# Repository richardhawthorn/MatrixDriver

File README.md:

### Description

ESP8266 board for driving neopixels arrays - <a href="http://www.matrixpainter.com">matrixpainter.com</a>

### Features

- ESP8266 12/12E Processor
- Power jack for 5v input
- Wifi connected
- Neopixel output (3.3v or 5v)
- Mini USB power connector
- FTDI programming port
- Surface mount

### Instructions

Setup an account at <a href="http://www.matrixpainter.com">matrixpainter.com</a> to start painting your pixels!

### License

This work is licensed under a Creative Commons Attribution-ShareAlike 4.0 International License.

<br />
Designed by <a xmlns:cc="http://creativecommons.org/ns#" href="http://www.richardhawthorn.com" property="cc:attributionName" rel="cc:attributionURL" target="_blank">Richard Hawthorn</a><br />
<a rel="license" href="http://creativecommons.org/licenses/by-sa/4.0/" target="_blank">View License</a>

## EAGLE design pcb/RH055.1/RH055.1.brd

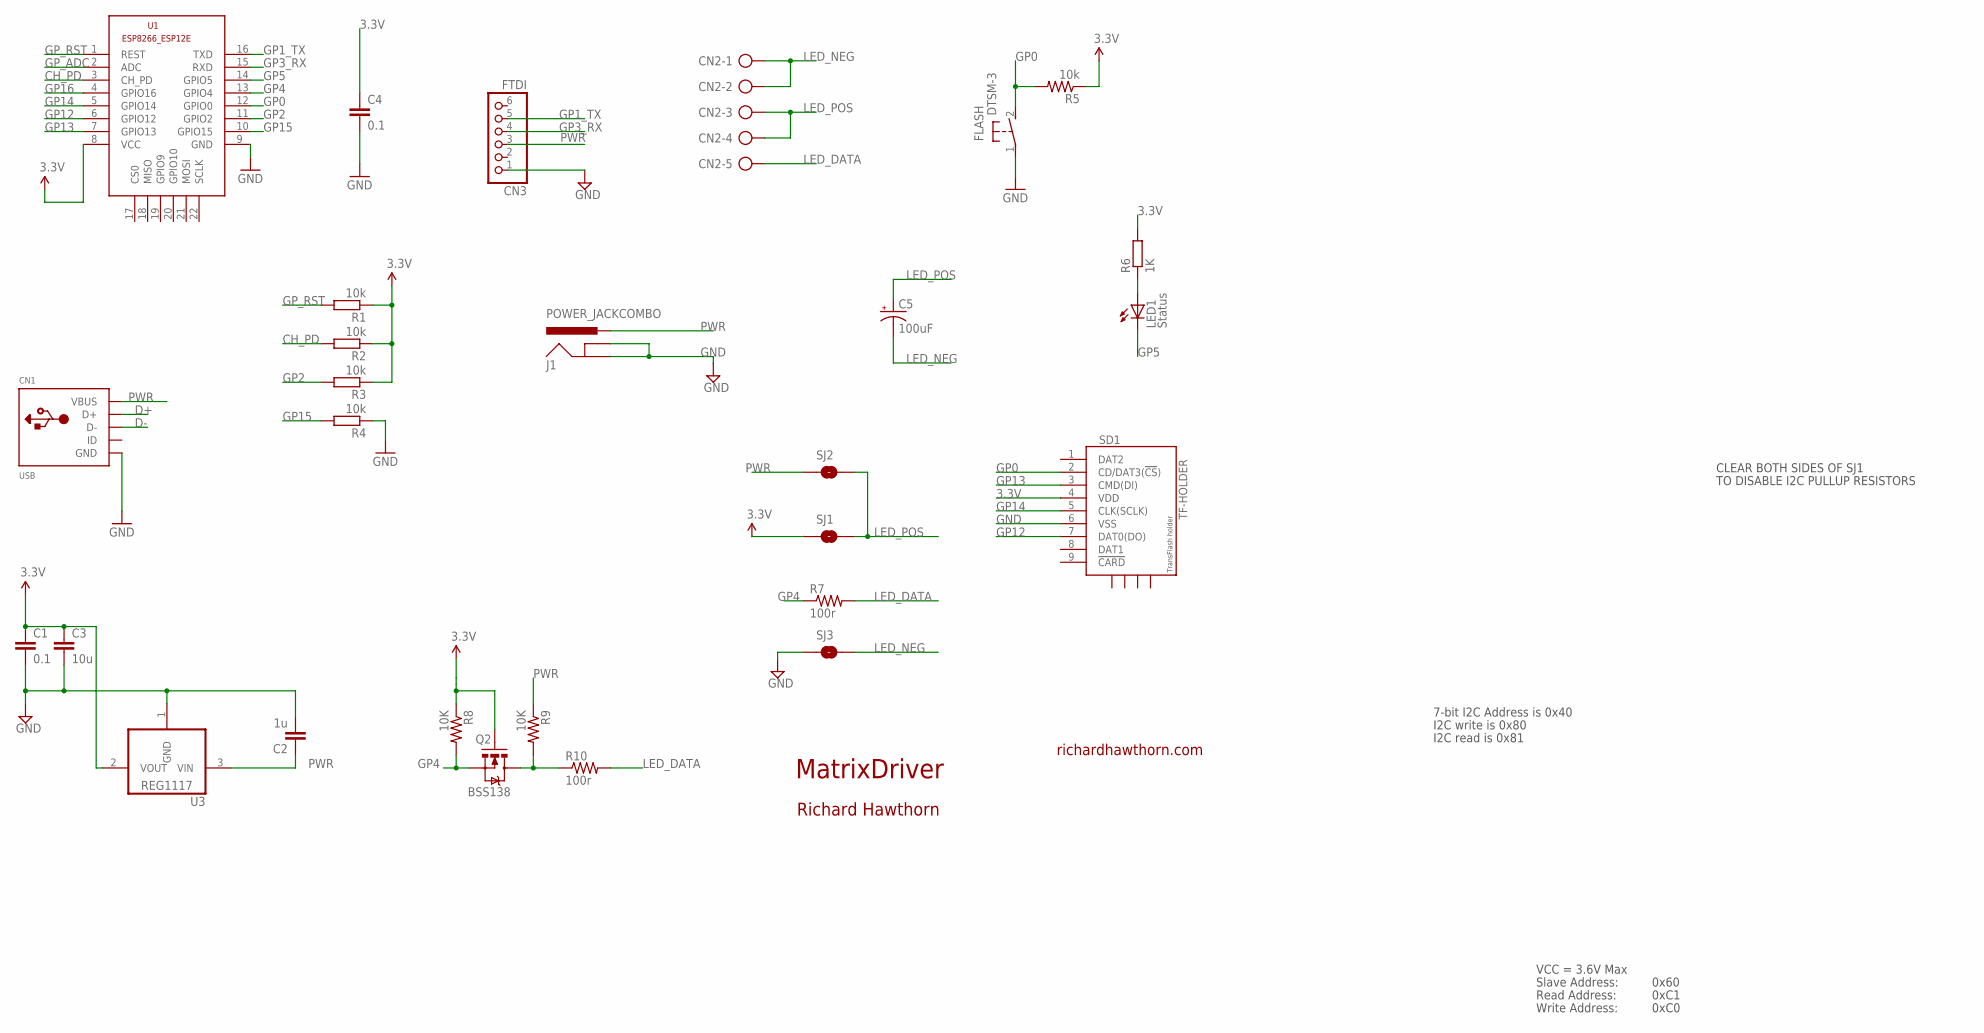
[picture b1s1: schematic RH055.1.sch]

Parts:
C1, C4: 0.1; 0603-CAP
C2: 1u; 0603-CAP
C3: 10u; 0805-CAP
C5: 100uF; EIA7343
CN1: USB; USB-MINIB
CN2: AK500/5
CN3: FTDI; 1X06
FLASH: DTSM-3
J1: POWER_JACKCOMBO; POWER_JACK_COMBO
LED1: Status; CHIPLED_0805
Q2: BSS138; SOT23-3
R1, R2, R3, R4: 10k; R0603
R5: 10k; 0805
R6: 1K; R0603
R7, R10: 100r; 0603-RES
R8, R9: 10K; 0805
SD1: TF-HOLDER; TF-PULL
SJ1, SJ2, SJ3: SOLDERJUMPERNO; SJ_2S-NO
U1: ESP8266-12EESP8266-ESP12E; ESP8266-ESP12E
U3: REG1117; SOT223

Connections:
3.3V: C1.1, C3.1, C4.1, Q2.1 (G), R1.1, R2.1, R3.1, R5.1, R6.2, R8.1, SD1.4 (VDD), SJ1.1, U1.8 (VCC), U3.2 (VOUT)
CH_PD: R2.2, U1.3 (CH_PD)
D+: CN1.D+
D-: CN1.D-
GND: C1.2, C2.2, C3.2, C4.2, CN1.GND, CN3.1, FLASH.1, J1.GND (GNDBREAK), J1.GND@1 (GND), R4.1, SD1.6 (VSS), SJ3.1, U1.9 (GND), U3.1 (GND)
GP0: FLASH.2, R5.2, SD1.2 (CD/DAT3(!CS!)), U1.12 (GPIO0)
GP1_TX: CN3.5, U1.16 (TXD)
GP2: R3.2, U1.11 (GPIO2)
GP3_RX: CN3.4, U1.15 (RXD)
GP4: Q2.2 (S), R7.1, R8.2, U1.13 (GPIO4)
GP5: LED1.C, U1.14 (GPIO5)
GP12: SD1.7 (DAT0(DO)), U1.6 (GPIO12)
GP13: SD1.3 (CMD(DI)), U1.7 (GPIO13)
GP14: SD1.5 (CLK(SCLK)), U1.5 (GPIO14)
GP15: R4.2, U1.10 (GPIO15)
GP16: U1.4 (GPIO16)
GP_ADC: U1.2 (ADC)
GP_RST: R1.2, U1.1 (REST)
HV_LED: Q2.3 (D), R9.2, R10.1
LED_DATA: CN2.5, R7.2, R10.2
LED_NEG: C5.C (-), CN2.1, CN2.2, SJ3.2
LED_POS: C5.A (+), CN2.3, CN2.4, SJ1.2, SJ2.2
unnamed: LED1.A, R6.1
PWR: C2.1, CN1.VBUS, CN3.3, J1.POWER (PWR), R9.1, SJ2.1, U3.3 (VIN)

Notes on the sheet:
MatrixDriver
richardhawthorn.com
Richard Hawthorn
CLEAR BOTH SIDES OF SJ1
TO DISABLE I2C PULLUP RESISTORS
7-bit I2C Address is 0x40
I2C write is 0x80
I2C read is 0x81
VCC = 3.6V Max
Read Address:
Write Address:
Slave Address:
0x60
0xC1
0xC0

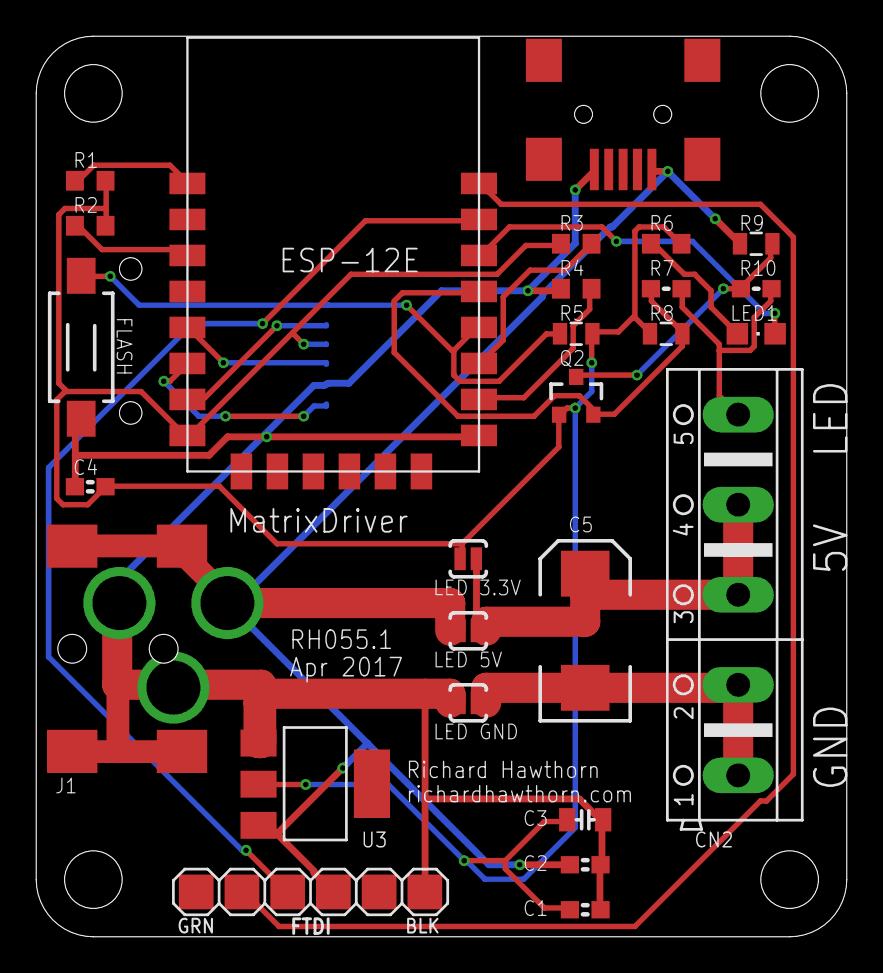
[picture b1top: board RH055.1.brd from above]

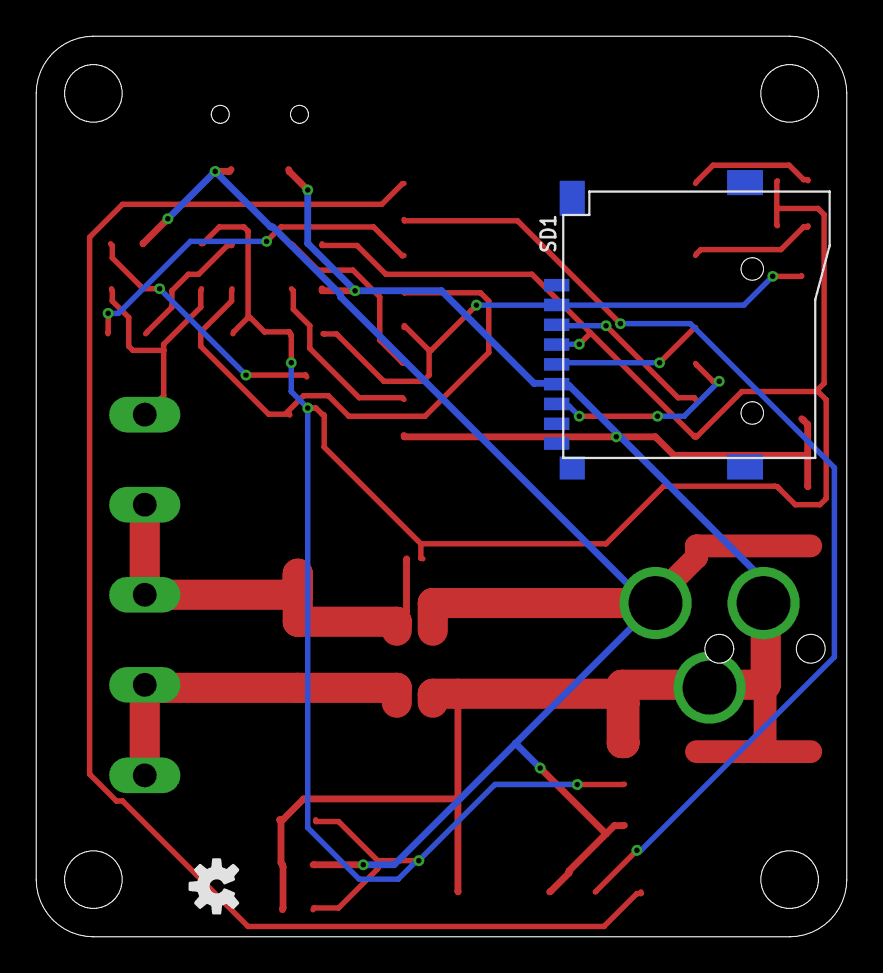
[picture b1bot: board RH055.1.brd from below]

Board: 2 copper layers, 45.0 x 50.0 mm, 29 parts (2 on the bottom side), 20 nets.

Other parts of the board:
U$3: OSHW-LOGO-S

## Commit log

2018-01-28 Add first version
2018-01-28 add readme
2018-01-28 add images
2018-01-29 add pcb images

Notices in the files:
parts and their libraries:
SparkFun-Aesthetics: Licensing: CC v3.0 Share-Alike You are welcome to use this library for commercial purposes.
SparkFun-Connectors: Licensing: Creative Commons ShareAlike 4.0 International - https://creativecommons.org/licenses/by-sa/4.0
